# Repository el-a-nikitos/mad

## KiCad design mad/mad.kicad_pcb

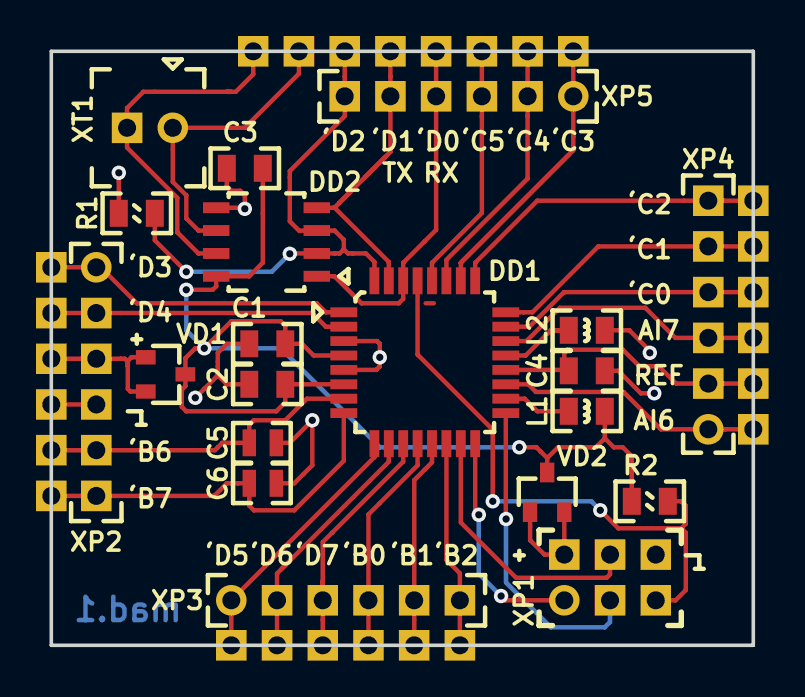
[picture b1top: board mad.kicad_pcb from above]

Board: 2 copper layers, 39.0 x 33.0 mm, 24 parts (0 on the bottom side), 34 nets.

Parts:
C1, C2, C3, C4: 10uF_0805; Конденсатор_SMD_0805
C5, C6: 0603; Конденсатор_SMD_0603
DD1: ATmega8A-AU; микросхема_ATMEGA-8-161AU
DD2: 5559ИН10_28(UART-RS485); SO-8
L1, L2: 10uH_0805; Чип-индуктивность_SMD_0805
R1, R2: 20k_0805; Резистор_SMD_0805_0,125Вт
VD1, VD2: BAR43CFILM; Диод_BAR43CFILM_SOT-23
X1, X2, X3: Вилка_PLS6; Полуотверстия_6_шт
X4: Вилка_PLS8; Полуотверстия_8_шт
XP1: Вилка_PLD6_ПРОГ; Вилка_PLD6_вертикальная
XP2, XP3, XP4, XP5: Вилка_PLS6; Вилка_PLS6_вертикальная
XT1: Клеммник_х2; Клеммник_х2_шаг2.54

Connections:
/ADC6: DD1.19, X3.1, XP4.1
/ADC7: DD1.22, X3.3, XP4.3
/AREF: C4.2, DD1.20, X3.2, XP4.2
/A_GND: DD1.21, L2.1
/A_VCC: DD1.18, L1.1
/EN: DD1.32, DD2.2, DD2.3, R1.1, X4.6, XP5.6
/GND: C1.1, C2.1, C3.1, C4.1, C5.1, C6.1, DD1.3, DD1.5, DD2.5, L2.2, R1.2, X1.4, XP1.6, XP2.4
/MISO: DD1.16, XP1.1
/MOSI: DD1.15, XP1.4
/PB0: DD1.12, X2.4, XP3.4
/PB1: DD1.13, X2.5, XP3.5
/PB2: DD1.14, X2.6, XP3.6
/PB6: C5.2, DD1.7, X1.5, XP2.5
/PB7: C6.2, DD1.8, X1.6, XP2.6
/PC0: DD1.23, X3.4, XP4.4
/PC1: DD1.24, X3.5, XP4.5
/PC2: DD1.25, X3.6, XP4.6
/PC3: DD1.26, X4.1, XP5.1
/PC4: DD1.27, X4.2, XP5.2
/PC5: DD1.28, X4.3, XP5.3
/PD3: DD1.1, X1.1, XP2.1
/PD4: DD1.2, X1.2, XP2.2
/PD5: DD1.9, X2.1, XP3.1
/PD6: DD1.10, X2.2, XP3.2
/PD7: DD1.11, X2.3, XP3.3
/RES: DD1.29, R2.1, XP1.5
/RS_A: DD2.6, X4.7, XT1.1
/RS_B: DD2.7, X4.8, XT1.2
/RX: DD1.30, DD2.1, X4.4, XP5.4
/SCK: DD1.17, XP1.3
/TX: DD1.31, DD2.4, X4.5, XP5.5
/VCC: C1.2, C2.2, C3.2, DD1.4, DD1.6, DD2.8, L1.2, R2.2, VD1.2, VD2.2
/VCC_IN: VD1.1, X1.3, XP2.3
/VCC_prog: VD2.1, XP1.2

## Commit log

2019-02-10 проект модуля atmega8 (39x33) с полуотверстиями
    +gerber файлы для заказа
2019-02-26 незначительные изменения
2019-03-14 начата работа над функцией прошивки модуля ввода/вывода
